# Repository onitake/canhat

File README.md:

# CAN HAT for Raspberry Pi Zero

Look! A hat! :tophat:

This little board extends the Raspberry Pi with a CAN interface, a 5V regulator
to supply the Pi with power and a pin header to access some GPIO lines.

## Specifications

### Mechanical

The board outline and component placement conform to the [Micro HAT specification]
and the [Add-On Boards and HATs] specification. It is designed to fit the
Raspberry Pi Zero, but can also be mounted to other models. (Pi 2, 3, 4, ...)

Instead of the usual DB9 connector found on many CAN interface boards, the
CAN HAT has terminal blocks for easier wiring and a smaller footprint.

For added stability, 11mm spacers should be mounted between the Pi and the HAT.

### Electronics

The circuit is built around the Microchip MCP2515 CAN Interface Controller,
connected to SPI port 0 on the Raspberry Pi, and a CAN transceiver IC.

It is highly recommended to use a 5V CAN transceiver with a separate 3.3V
input for the RX/TX pins, such as Texas Instruments SN65HVD541.
When using a different transceiver without split voltage, the voltage inputs
must be reconfigured through solder bridges JP3 and JP4.

The SN65HVD541 also supports disabling the transceiver through pin 8.
This pin is connected to ground via JP2 and 0Ω resistor R5 by default,
which enables the transceiver at full speed. With JP2, it can be connected
to Raspberry Pi pin GPIO22, which makes it controllable. Not that this is not
supported by the MCP2515 device drivers and must be implemented manually.
R5 is useful for transceivers that support slope control, but this is not
available in the SN65HVD541.

See the section "Transceiver Configuration" below.

To reduce interference on the CAN bus, tuned microstrips were used to
connect the CAN transceiver to the terminals on the PCB. The differential
impedance is matched to 60Ω. For added fun, the pair length is also matched
with meanders.

Aside from the CAN interface part, an additional ID EEPROM ensures conformance
with the HAT specification. JP1 is only needed to program the EEPROM. The part
can be left out if desired, and the connection be made by other means, such as
a screwdriver or a temporary solder bridge.

The left side of the board is populated with a 6-24V to 5V step-down converter.
If the Raspberry Pi is powered via USB, the components for this converter
should not be soldered, or at least not be connected to a power source.
It's also possible to power the Rasberry Pi from a 5V source via this
connector directly. See the section "Power Options" below.

Note that the AP63205 regulator is rated for a maximum current of 2A.
The [Add-On Boards and HATs] specification recommends at least 2.5A, but 2A
is normally sufficient unless a lot of peripherals and USB devices are used.
The Raspberry Pi 3 and the CAN HAT will only draw a few hundred mA when using
Ethernet and the CAN bus and no other external peripherals.

Overvoltage protection is done through the TVS diode D1, but note it cannot
handle overcurrent. The fuse may not react quickly enough if a large amount
of energy is sent through D1, and it may still fail to protect the circuit.

### Transceiver Configuration

The recommended transceiver SN65HVDA541 has separate voltage inputs for
the logic and the CAN transceiver. In the default configuration, the logic
is connected to 3.3V and the transceiver to 5V.

If transceiver power control should be possible from the Raspberry Pi,
cut the solder bridge from JP2 (IOCTL) pins 1-2 and connect 2-3 instead.
Note that this is not supported by the driver and must be implemented
separately.

For over transceivers, the 3.3V power supply should be disconnected by
cutting JP3 (3VIO) and choosing an appropriate voltage on JP4 (VBUS).
1-2 is 5V and 2-3 is 3.3V. Note that there is no input voltage protection
on the MCP2515, which is powered from 3.3V. Choosing a 5V part may result
in damage to the MCP2515.

If the chosen transceiver supports slope control on pin 8, JP2 should be
left in position 1-2 and the 0Ω resistor R5 should be replaced with an
appropriate value. Refer to the transceiver's data sheet for more information.

### Power Options

:warning: **Do not supply power to the Raspberry Pi and J5 at the same time!**

The CAN hat can backpower the Raspberry Pi, but it can also be powered by it.

The following configurations are supported:

#### All power on Raspberry Pi

If you're already powering the Raspberry Pi from a 5V source (such as USB),
you don't need the regulator circuit on the CAN hat.

Leave out the parts J5, F2, D1, D2, C9, U4, C10, L1, C12 and C13.

#### 5V power on CAN hat

In this configuration, 5V is delivered directly from the hat to the RPi.

Leave out the parts F2, D1, D2, C9, U4, C10, L1, C12 and C13, but connect
the solder bridge JP5.

#### 12V power on CAN hat

If you only have a 12V power source available, you can populate the step-down
voltage regulator on the CAN hat, which will convert the input to 5V and feed
it to the Raspberry Pi.

Keep the solder bridge JP5 disconnected, or you may damage your Raspberry Pi!

Input polarity reversal and overvoltage is protected by D2 and D1, but you
should still make sure not to swap the polarity on the 12V input.
Failure to do so could lead to a short-circuit via other bus components.

## Cabling and Termination

It is recommended to use twisted pair or star quad cabling to connect other
CAN nodes. With star quad cables, connect opposite wires together to the
same terminal for better noise resistance.

Use shielded cable if possible and make sure all CAN bus componentes share
a common ground. To facilitate connecting the bus ground, there is a ground
terminal for each CAN connection, marked with an earth sign (⏚).

If the Raspberry Pi is the last node in a chain, attach a 120Ω termination
resistor to the terminals marked with a downwards arrow (↓).

:warning: **Note the polarity on the terminals! CAN does not support swapping
the H/L pins.**

## GPIO Pins

For added convenience, 4 Raspberry Pi GPIO pins are available via an optional
connector on the board. If you would like to use them, solder the J3 header.

R11, R12, R13, R14 are optional pull-up resistors. When using the GPIO lines
as external inputs, you can solder 1k-10k resistors into them. A ground pin
for toggling the logic level is available on the pin header.

The 4 GPIO lines are: GPIO19, GPIO20, GPIO21, GPIO26. GPIO19-21 are also
available for SPI, but this requires custom configuration and is outside
the scope of the CAN HAT.

Note: To actually use the GPIO pins, you must edit eeprom_settings.txt to
suit your custom configuration, or enable the GPIO pins from user space
after booting the Raspberry Pi.

## Integration

The built-in ID EEPROM contains device information according to the
[HAT ID EEPROM Specification], as well as a Device Tree blob. This allows for
automatic configuration when Linux boots.

The EEPROM can be programmed in the field by shorting the jumper JP1 and
flashing with the help of [eepromutils].

The provided Makefile will compile a DeviceTree overlay and the device descriptor
into an EEPROM image. To build the image, type:

    make

To flash the image to the attached EEPROM, you first need to allow access to
the first I²C bus. On the Raspberry Pi, this bus is used for several system
components, and hidden by default to avoid accidental access. Put the following
line into `/boot/config.txt`:

    dtparam=i2c_vc=on

Short the write protection jumper, reboot, and flash the EEPROM:

    sudo make flash

Remove the line from `/boot/config.txt` and the jumper, then reboot.

The preconfigured I²C bus and and device address correspond with the AT24C32E
chip on the HAT. Change them in the Makefile if you use a different device.

The CAN bus should then appear automatically as network device `can0`.

## Compatibility

The HAT is fully compatible with the Linux drivers for the MCP2551.
Refer to the [CAN bus on raspberry pi quick guide] for more information
on how to configure the device manually.

This may be necessary on older Raspberry Pi boards that don't support the
ID EEPROM feature.

During testing, you can use the following command to quickly load the driver
without the ID EEPROM:

    sudo dtoverlay mcp2515-can0 oscillator=16000000 interrupt=12

Note that the interface still needs to be brought up like a network device:

    sudo ip link set can0 up type can bitrate 125000 loopback off sample-point 0.75

This configures a line speed of 1MHz. Commonly supported rates are 125kHz or
1MHz. Choose according to your other CAN components and wiring quality.

## Links

[Add-On Boards and HATs]: https://github.com/raspberrypi/hats
[Micro HAT Specification]: https://github.com/raspberrypi/hats/blob/master/uhat-board-mechanical.pdf
[HAT ID EEPROM Specification]: https://github.com/raspberrypi/hats/blob/master/eeprom-format.md
[CAN bus on raspberry pi quick guide]: https://www.raspberrypi.org/forums/viewtopic.php?t=141052
[eepromutils]: https://github.com/raspberrypi/hats/tree/master/eepromutils
[Overview of 3.3V CAN Transceivers]: http://www.ti.com/lit/an/slla337/slla337.pdf

### Data Sheets

* [Microchip MCP2515 CAN Interface Controller](https://www.microchip.com/wwwproducts/en/en010406)
* [Microchip MCP2551](http://ww1.microchip.com/downloads/en/devicedoc/21667e.pdf)
* [Texas Instruments SN65HVD234 3.3 V CAN Transceiver](http://www.ti.com/product/SN65HVD234)
* [Microchip AT24C32E 32Kbit Serial EEPROM](https://www.microchip.com/wwwproducts/en/AT24C32E)
* [Diodes Inc AP63205 Buck Regulator](https://www.diodes.com/assets/Datasheets/AP63200-AP63201-AP63203-AP63205.pdf)

## Legal

This circuit, schematics, board layouts and accompanying documentation is
Copyright © 2019-2022 by Gregor Riepl

You may use it under the terms of the CERN Open Hardware Licence, version v1.2.

Raspberry Pi is a trademark of the Raspberry Pi Foundation.

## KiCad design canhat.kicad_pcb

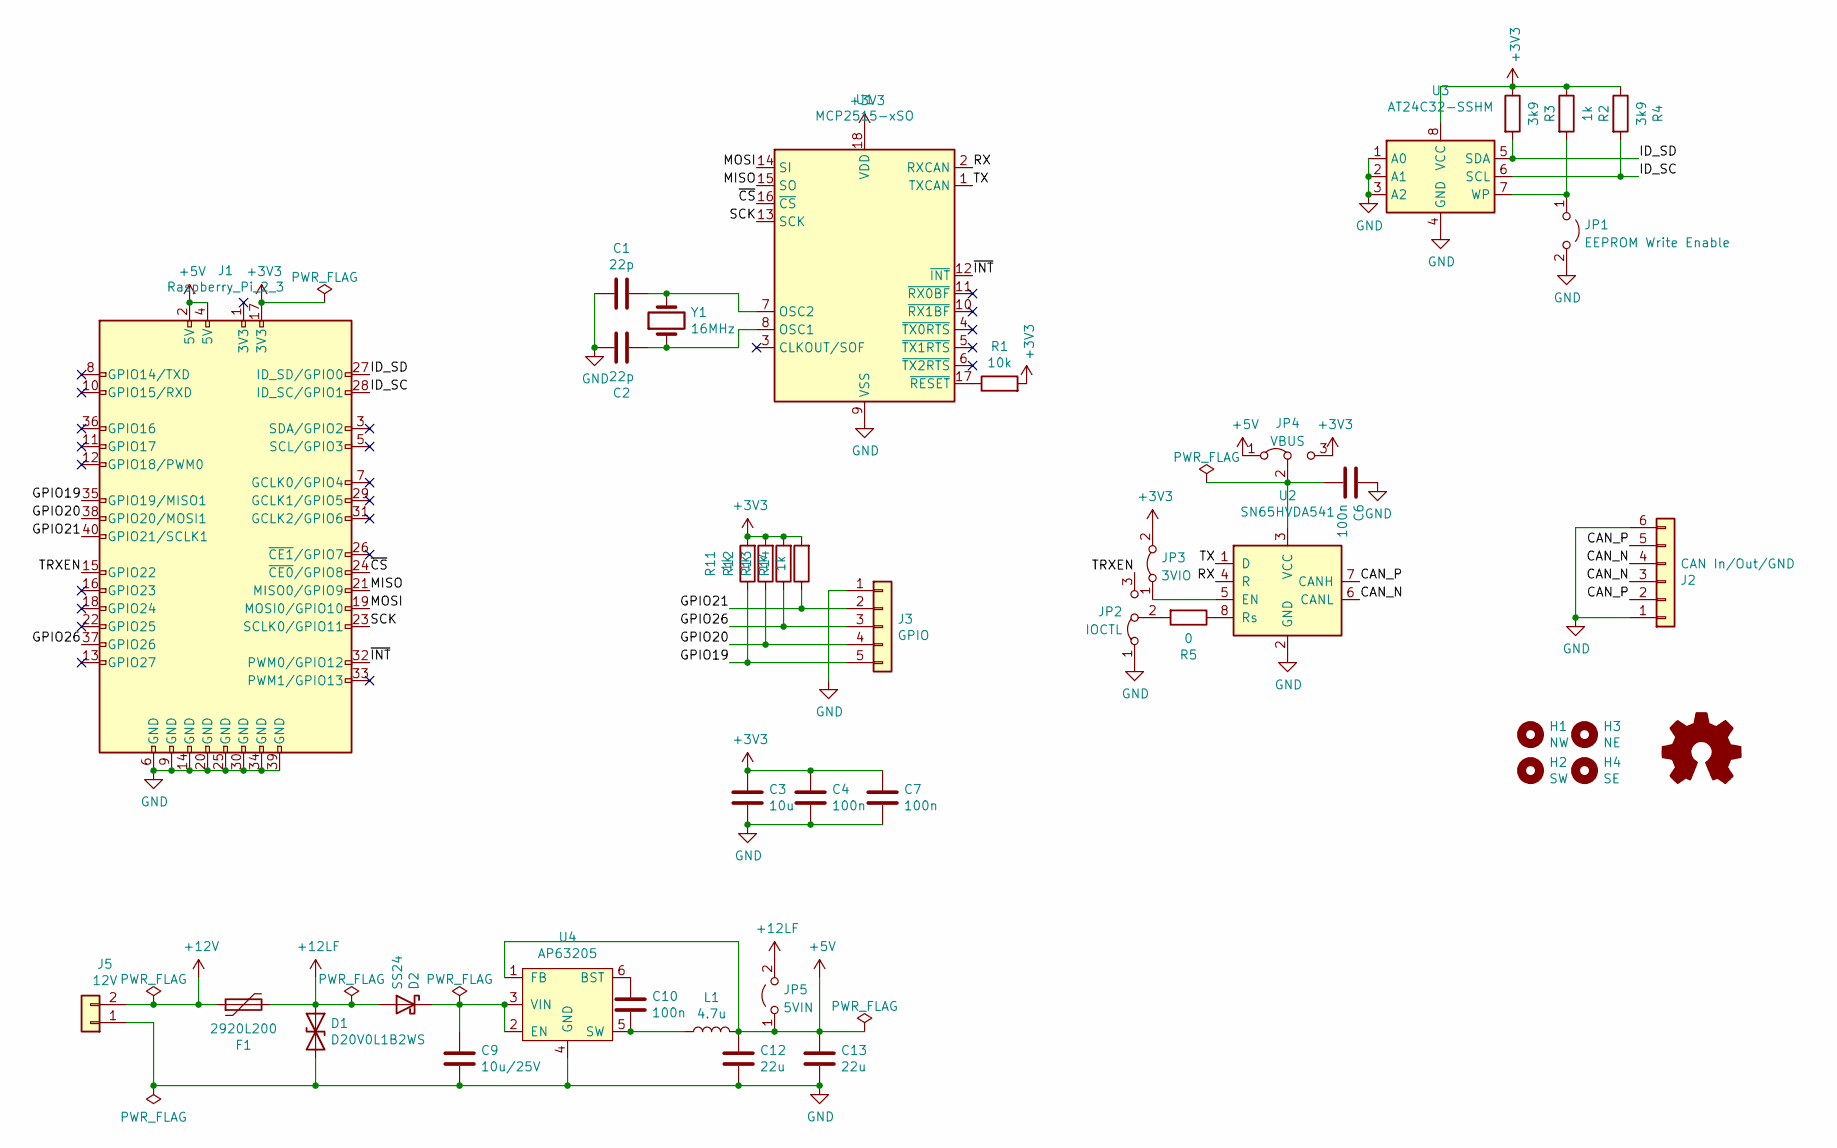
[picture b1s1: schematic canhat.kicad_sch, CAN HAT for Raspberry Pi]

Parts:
C1, C2: 22p; C_0805_2012Metric_Pad1.18x1.45mm_HandSolder
C3: 10u; C_0805_2012Metric_Pad1.18x1.45mm_HandSolder
C4, C6, C7, C10: 100n; C_0805_2012Metric_Pad1.18x1.45mm_HandSolder
C9: 10u/25V; C_0805_2012Metric_Pad1.18x1.45mm_HandSolder
C12, C13: 22u; C_0805_2012Metric_Pad1.18x1.45mm_HandSolder
D1: D20V0L1B2WS; D_SOD-323_HandSoldering
D2: SS24; D_SMA_Handsoldering
F1: 2920L200; Fuse_2920_7451Metric_Pad2.10x5.45mm_HandSolder
H1: NW; MountingHole_2.7mm
H2: SW; MountingHole_2.7mm
H3: NE; MountingHole_2.7mm
H4: SE; MountingHole_2.7mm
J1: Raspberry_Pi_2_3; PinSocket_2x20_P2.54mm_Vertical
J2: CAN In/Out/GND; TerminalBlock_Phoenix_MPT-0,5-6-2.54_1x06_P2.54mm_Horizontal
J3: GPIO; PinHeader_1x05_P2.54mm_Vertical
J5: 12V; TerminalBlock_Phoenix_MPT-0,5-2-2.54_1x02_P2.54mm_Horizontal
JP1: EEPROM Write Enable; PinHeader_1x02_P2.54mm_Vertical
JP2: IOCTL; SolderJumper-3_P1.3mm_Bridged12_RoundedPad1.0x1.5mm_NumberL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
JP3: 3VIO; SolderJumper-2_P1.3mm_Bridged_RoundedPad1.0x1.5mm
JP4: VBUS; SolderJumper-3_P1.3mm_Bridged12_RoundedPad1.0x1.5mm_NumberL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
JP5: 5VIN; SolderJumper-2_P1.3mm_Open_RoundedPad1.0x1.5mm
L1: 4.7u; L_TDK_SLF7032
OSHW1: Logo_Open_Hardware_Small; OSHW-Logo_5.7x6mm_SilkScreen
R1: 10k; R_0805_2012Metric_Pad1.20x1.40mm_HandSolder
R2, R11, R12, R13, R14: 1k; R_0805_2012Metric_Pad1.20x1.40mm_HandSolder
R3, R4: 3k9; R_0805_2012Metric_Pad1.20x1.40mm_HandSolder
R5: 0; R_0805_2012Metric_Pad1.20x1.40mm_HandSolder
U1: MCP2515-xSO; SOIC-18W_7.5x11.6mm_P1.27mm
U2: SN65HVDA541; SOIC-8_3.9x4.9mm_P1.27mm
U3: AT24C32-SSHM; SOIC-8_3.9x4.9mm_P1.27mm
U4: AP63205; TSOT-23-6
Y1: 16MHz; Crystal_SMD_HC49-SD

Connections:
+3V3: C3.1, C4.1, C7.1, J1.17 (3V3), JP3.2 (B), JP4.3 (B), R1.2, R2.1, R3.1, R4.1, R11.2, R12.2, R13.2, R14.2, U1.18 (VDD), U3.8 (VCC)
+5V: C12.1, C13.1, J1.2 (5V), J1.4 (5V), JP4.1 (A), JP5.1 (A), L1.2, U4.1 (FB)
+12LF: D1.1 (A1), D2.2 (A), F1.2, JP5.2 (B)
+12V: F1.1, J5.2
/CAN_N: J2.3, J2.4, U2.6 (CANL)
/CAN_P: J2.2, J2.5, U2.7 (CANH)
/GPIO19: J1.35 (GPIO19/MISO1), J3.5, R11.1
/GPIO20: J1.38 (GPIO20/MOSI1), J3.4, R12.1
/GPIO21: J1.40 (GPIO21/SCLK1), J3.2, R14.1
/GPIO26: J1.37 (GPIO26), J3.3, R13.1
/ID_SC: J1.28 (ID_SC/GPIO1), R4.2, U3.6 (SCL)
/ID_SD: J1.27 (ID_SD/GPIO0), R3.2, U3.5 (SDA)
/MISO: J1.21 (MISO0/GPIO9), U1.15 (SO)
/MOSI: J1.19 (MOSI0/GPIO10), U1.14 (SI)
/RX: U1.2 (RXCAN), U2.4 (R)
/SCK: J1.23 (SCLK0/GPIO11), U1.13 (SCK)
/TRXEN: J1.15 (GPIO22), JP2.3 (B)
/TX: U1.1 (TXCAN), U2.1 (D)
/~CS: J1.24 (~CE0/GPIO8), U1.16 (~CS)
/~INT: J1.32 (PWM0/GPIO12), U1.12 (~INT)
GND: C1.2, C2.2, C3.2, C4.2, C6.1, C7.2, C9.2, C12.2, C13.2, D1.2 (A2), J1.6 (GND), J1.9 (GND), J1.14 (GND), J1.20 (GND), J1.25 (GND), J1.30 (GND), J1.34 (GND), J1.39 (GND), J2.1, J2.6, J3.1, J5.1, JP1.2 (B), JP2.1 (A), U1.9 (VSS), U2.2 (GND), U3.1 (A0), U3.2 (A1), U3.3 (A2), U3.4 (GND), U4.4 (GND)
unnamed: C1.1, U1.7 (OSC2), Y1.2
unnamed: C2.1, U1.8 (OSC1), Y1.1
unnamed: C6.2, JP4.2 (C), U2.3 (VCC)
unnamed: C9.1, D2.1 (K), U4.2 (EN), U4.3 (VIN)
unnamed: C10.1, U4.6 (BST)
unnamed: C10.2, L1.1, U4.5 (SW)
unnamed: JP1.1 (A), R2.2, U3.7 (WP)
unnamed: JP2.2 (C), R5.2
unnamed: JP3.1 (A), U2.5 (EN)
unnamed: R1.1, U1.17 (~RESET)
unnamed: R5.1, U2.8 (Rs)

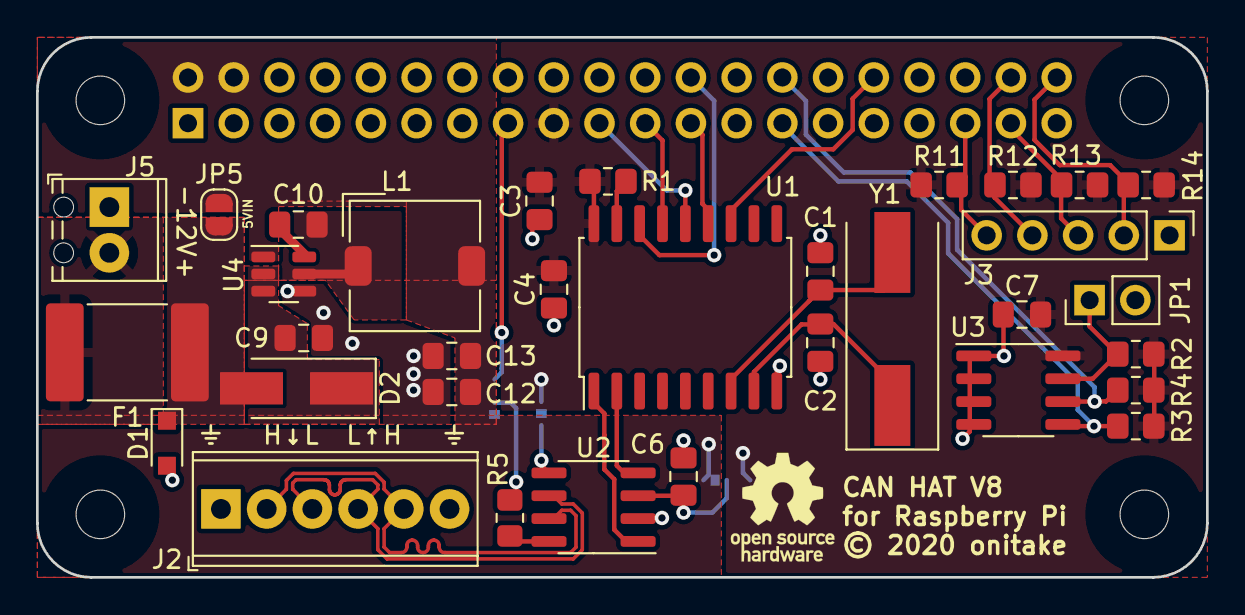
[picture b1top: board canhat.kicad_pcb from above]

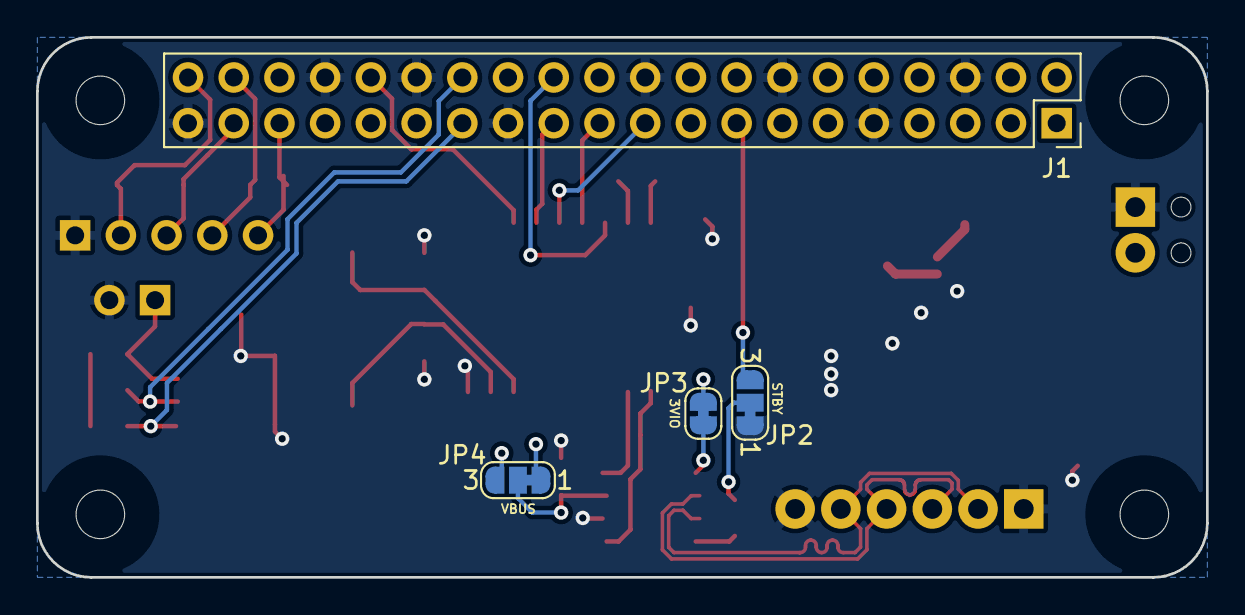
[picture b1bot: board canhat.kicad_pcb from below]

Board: 2 copper layers, 65.0 x 30.0 mm, 42 parts (4 on the bottom side), 32 nets.

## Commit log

2019-04-02 Added readme and license
2019-04-02 Added gitignore
2019-04-02 Added schematics and board
2019-04-02 Improved refs
2019-04-02 Better link list
2019-04-02 Added eepromutils link
2019-04-02 Added I2C pullups and CAN microstrip
2019-04-02 Improved routing
2019-04-02 Added built EEPROM files to gitignore
2019-04-02 Added EEPROM and DeviceTree overlay
2019-04-02 Added instructions for building and flashing the EEPROM
2019-04-02 Corrected 1k pullup
2019-04-03 Replaced 5V parts with 3.3V and added slew control res
2019-04-03 Updated documentation
2019-04-03 Fixed markdown links
2019-04-03 Removed references to non-reference links as that isn't supported on GH
2019-04-04 Added/updated sheet metadata
2019-04-06 Optimized some traces
2019-04-06 Added production files to ignore list
2019-04-06 Unplated mounting holes
2019-04-06 Prepare for manufacturing
2019-04-16 Fixed EEPROM I2C address
2019-04-30 Replaced CAN terminals with single block
2019-05-01 Added 5V power terminal
2019-05-02 Optimized traces
2019-05-02 Updated readme with infos for V2
2019-05-02 Small track optimisations
2019-05-02 Added board image
2019-05-11 Added new preview imae
2019-05-11 Split off power plane for transceiver for 3.3/5V power
2019-05-11 Explain split power plane
2019-05-14 Non-planar Vcc/Vbus wiring
2019-05-14 Release v2
2019-05-15 Redid layout to shorten long traces
2019-05-15 Small optimizations
2019-05-15 Emphasize important readme points
2019-05-15 Cosmetics
2019-05-23 Added protective resistors between xceiver and controller
2019-11-12 Added 12V step-down power supply
2019-11-12 Removed obsolete PSU and added missing 3.3V cap
2019-11-13 Routing and tweaking
2019-11-14 Added direct-5V jumper
2019-11-19 Fine tuning
2019-11-19 Updated screenshot
2019-11-19 Updated readme for new circuit layout
2019-11-19 Added note about polarity protection diode
2019-11-21 Board image fine tuning
2020-01-28 Added datasheet link to regulator
2020-01-28 Added front ground to optimize dissipation
2020-01-28 Updated board rev
2020-02-15 Replaced input cap with 0805
2020-02-16 Added GPIO pullups
2020-06-20 Fixed incorrect feedback pin wire
2020-07-11 Replace terminals with DB9 connectors
2020-07-13 Reordered parts an added GPIO pins
2020-07-13 Ignore cache
2020-07-13 Move parts a bit
2020-07-18 More finetuning
2020-07-19 Some more finetunings
2020-07-19 Updated schema revision
2020-07-19 Corrected Raspberry Pi branding
2020-07-19 Updated readme with current design specifics
2020-07-19 New board rendering
2020-07-24 Use 5V transceiver with 3V logic and some finetuning
2020-07-26 Trace/power plane fine tuning
2020-07-26 Improve flashing instructions
2020-07-26 Update readme with new power/transceiver specs
2021-03-02 Added TVS diode
2021-03-02 Remove clearance settings
2022-12-19 Convert to KiCAD6, update layout
2022-12-19 Update gitignore
2022-12-19 Cleanup
2022-12-20 Replaced resistors with solder bridges
2023-09-24 Some readme corrections, new 3D render

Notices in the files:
canhat.kicad_pcb:
© 2020 Gregor Riepl
© 2020 onitake
